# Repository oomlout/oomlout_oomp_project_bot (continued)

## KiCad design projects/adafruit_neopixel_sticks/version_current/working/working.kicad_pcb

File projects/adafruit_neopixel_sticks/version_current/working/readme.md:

# NeoPixel-Sticks by adafruit  
This is a harvested standardized copy of a project from github.  
The original project can be found at:  
https://github.com/adafruit/NeoPixel-Sticks  
Please consult that link for additional, details, files, and license information.  
Note: It was auto harvested and if the original repo had more than one board file or anything out of the ordinary the files here are likely not representative.

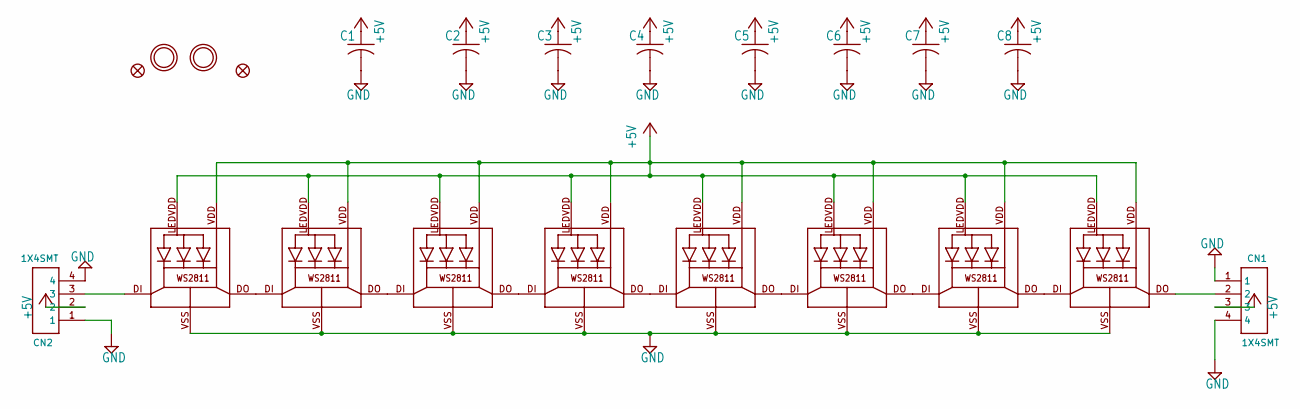
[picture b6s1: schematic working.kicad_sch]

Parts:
C1, C2, C3, C4, C5, C6, C7, C8: C-USC0805K; C0805K
CN1, CN2: 1X4SMT; 1X4-SMT
FID1, FID3: FIDUCIAL""; FIDUCIAL_1MM
LED1, LED2, LED3, LED4, LED5, LED6, LED7, LED8: WS28115050
U$2, U$3: MOUNTINGHOLE2.0; MOUNTINGHOLE_2.0_PLATED

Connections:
+5V: C1.1, C2.1, C3.1, C4.1, C5.1, C6.1, C7.1, C8.1, CN1.3, CN2.2, LED1.LEDVDD, LED1.VDD, LED2.LEDVDD, LED2.VDD, LED3.LEDVDD, LED3.VDD, LED4.LEDVDD, LED4.VDD, LED5.LEDVDD, LED5.VDD, LED6.LEDVDD, LED6.VDD, LED7.LEDVDD, LED7.VDD, LED8.LEDVDD, LED8.VDD
GND: C1.2, C2.2, C3.2, C4.2, C5.2, C6.2, C7.2, C8.2, CN1.1, CN1.4, CN2.1, CN2.4, LED1.VSS (GND), LED2.VSS (GND), LED3.VSS (GND), LED4.VSS (GND), LED5.VSS (GND), LED6.VSS (GND), LED7.VSS (GND), LED8.VSS (GND)
unnamed: LED1.DO, LED2.DI
unnamed: LED2.DO, LED3.DI
unnamed: LED3.DO, LED4.DI
unnamed: LED4.DO, LED5.DI
unnamed: LED5.DO, LED6.DI
unnamed: LED6.DO, LED7.DI
unnamed: LED7.DO, LED8.DI
unnamed: CN2.3, LED1.DI
unnamed: CN1.2, LED8.DO

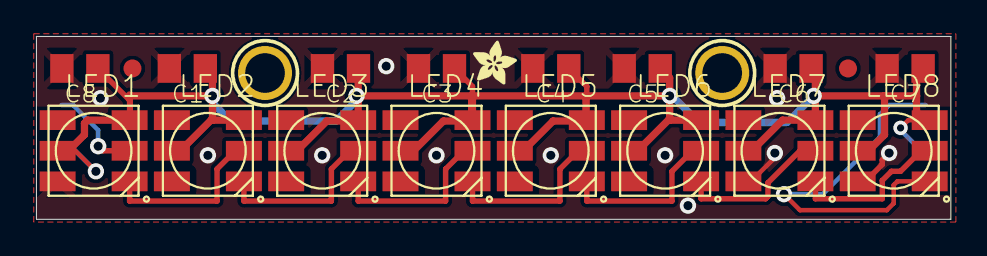
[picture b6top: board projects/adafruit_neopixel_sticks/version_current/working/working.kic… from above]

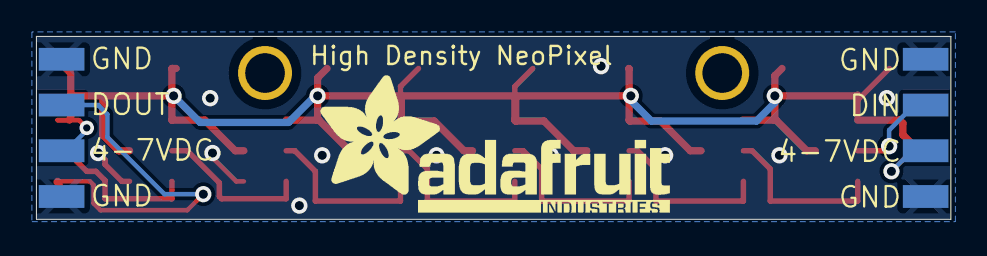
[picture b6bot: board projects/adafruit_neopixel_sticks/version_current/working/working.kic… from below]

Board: 2 copper layers, 50.8 x 10.2 mm, 24 parts (3 on the bottom side), 11 nets.

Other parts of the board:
U$1: ADAFRUIT_TEXT_20MM
U$4: ADAFRUIT_2.5MM

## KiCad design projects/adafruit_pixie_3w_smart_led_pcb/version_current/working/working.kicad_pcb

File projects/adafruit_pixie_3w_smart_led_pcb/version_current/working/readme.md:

# Pixie-3W-Smart-LED-PCB by adafruit  
This is a harvested standardized copy of a project from github.  
The original project can be found at:  
https://github.com/adafruit/Pixie-3W-Smart-LED-PCB  
Please consult that link for additional, details, files, and license information.  
Note: It was auto harvested and if the original repo had more than one board file or anything out of the ordinary the files here are likely not representative.

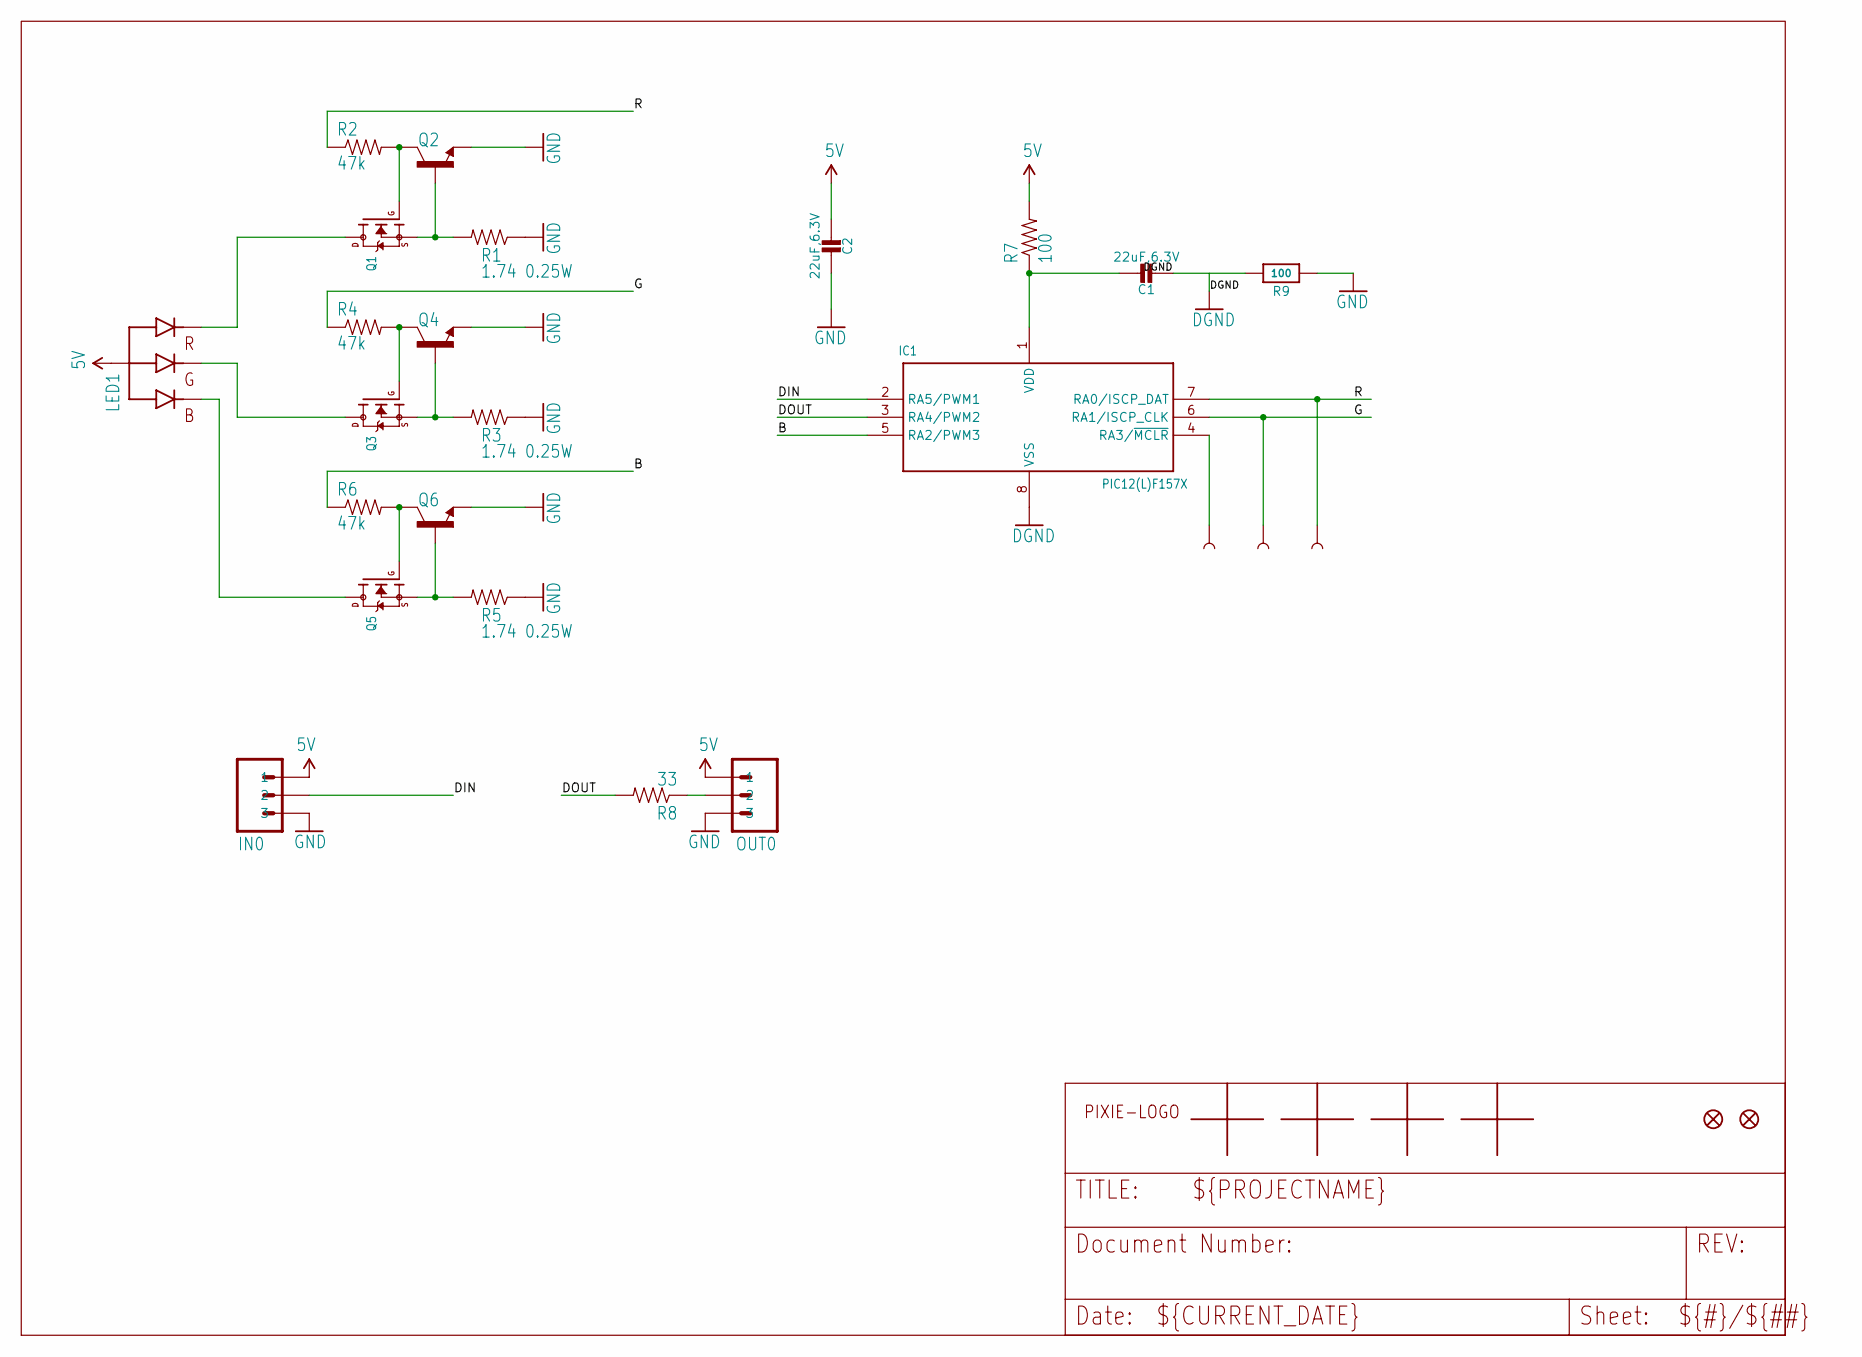
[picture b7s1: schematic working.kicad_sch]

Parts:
!MCLR0: TEST-POINT3X4; PAD.03X.04
C1, C2: 22uF,6.3V; _0805MP
IC1: PIC12(L)F157X; MSOP-8
IN0: M030.1PWR+SIG; 1X03-0.1PWR+SIG
LED1: RGBLED_CA; RGBLED3W4PIN
OUT0: M030.1PWR+SIG; 1X03-0.1PWR+SIG
PGC0: TEST-POINT3X4; PAD.03X.04
PGD0: TEST-POINT3X4; PAD.03X.04
Q1, Q3, Q5: IRLML2060TRPBF; SOT23-3
Q2, Q4, Q6: MMBT2222A; SOT23-3
R1, R3, R5: 1.74 0.25W; 1206
R2, R4, R6: 47k; 0603-RES
R7: 100; 0603-RES
R8: 33; 0603-RES
R9: 100; _0603MP
U$1, U$2, U$3, U$4: ALIGN_CROSS
U$5: PIXIE-LOGO
U$6, U$7: FIDUCIAL""; FIDUCIAL_1MM

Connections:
5V: C2.2, IN0.P$1 (1), LED1.ANODE (VCC), OUT0.P$1 (1), R7.2
B: IC1.5 (RA2/PWM3), R6.1
DGND: C1.2, IC1.8 (VSS), R9.2
DIN: IC1.2 (RA5/PWM1), IN0.P$2 (2)
DOUT: IC1.3 (RA4/PWM2), R8.2
G: IC1.6 (RA1/ISCP_CLK), PGC0.P$1, R4.1
GND: C2.1, IN0.P$3 (3), OUT0.P$3 (3), Q2.2 (E), Q4.2 (E), Q6.2 (E), R1.1, R3.1, R5.1, R9.1
unnamed: LED1.R (RED), Q1.3 (D)
unnamed: LED1.G (GREEN), Q3.3 (D)
unnamed: LED1.B (BLUE), Q5.3 (D)
unnamed: Q1.2 (S), Q2.1 (B), R1.2
unnamed: Q3.2 (S), Q4.1 (B), R3.2
unnamed: OUT0.P$2 (2), R8.1
unnamed: !MCLR0.P$1, IC1.4 (RA3/~MCLR)
unnamed: Q5.1 (G), Q6.3 (C), R6.2
unnamed: Q3.1 (G), Q4.3 (C), R4.2
unnamed: C1.1, IC1.1 (VDD), R7.1
unnamed: Q5.2 (S), Q6.1 (B), R5.2
unnamed: Q1.1 (G), Q2.3 (C), R2.2
R: IC1.7 (RA0/ISCP_DAT), PGD0.P$1, R2.1

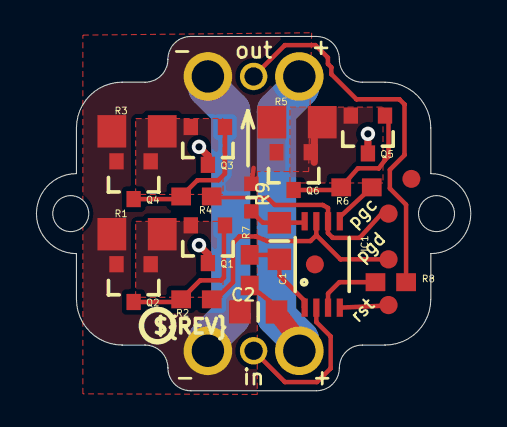
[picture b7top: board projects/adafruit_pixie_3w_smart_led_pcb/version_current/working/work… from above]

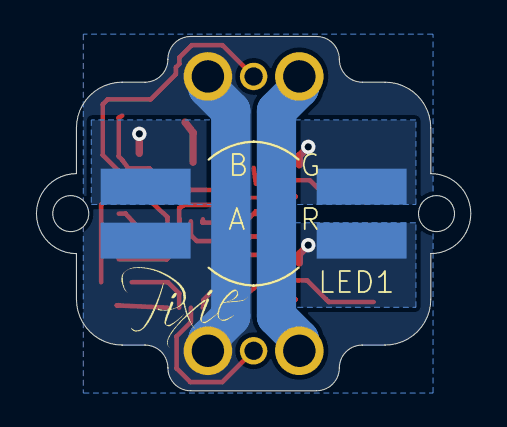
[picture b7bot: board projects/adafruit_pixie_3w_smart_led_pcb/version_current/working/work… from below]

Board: 16 copper layers, 24.1 x 19.7 mm, 34 parts (2 on the bottom side), 20 nets.

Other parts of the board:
@HOLE0, @HOLE1: (no value)
U$8: PCBFEAT-REV-040

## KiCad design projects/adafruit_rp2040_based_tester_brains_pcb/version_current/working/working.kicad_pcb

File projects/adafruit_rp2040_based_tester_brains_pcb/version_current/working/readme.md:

# OOMP Project  
## RP2040-Based-Tester-Brains-PCB  by adafruit  
  
oomp key: oomp_projects_flat_adafruit_rp2040_based_tester_brains_pcb  
(snippet of original readme)  
  
-- Adafruit RP2040 Based Tester Brains PCB  

PCB files for the Adafruit RP2040 Based Tester Brains.   
  
Format is EagleCAD schematic and board layout  
  
--- Description  
  
This board is what we use internally at Adafruit to program and test boards with microcontrollers on them.   
   * An [RP2040 Pico](https://www.adafruit.com/product/5525) (or perhaps PicoW?) is used to run the test software  
   * [Use a 16x2 LCD (ideally RGB backlight)](https://www.adafruit.com/product/398) for display output with color feedback such as green for pass, red for fail. RGB backlight is WS2811-controlled. Don't forget to set the contrast pot on first usage.  
   * Serial1 hardware UART has RX/TX pin switch to flip directions  
   * 1.9" TFT connector is placed but hasn't been tested or used yet  
   * Piezo buzzer can be used for audible feedback alerts  
   * STEMMA QT I2C port  
   * Big reset button  
   * Firmware files can be stored on MicroSD card which is slotted in.   
   * Connect the right hand side, either the 0.1" header or 18-pin EYESPI-like FPC connector to the device-under-test jig which can be different for each product.   
   * [USB Host testing is done with bitbang PIO support in TinyUSB](https://github.com/adafruit/Adafruit_TinyUSB_Arduino), USB 5V power can be turned on / off   
   * Use Philhower RP2040 core for programming  
   * The RP2040 brains can perform ESP32 programming, RP2040-via-USB, AVR ICSP/UPDI, or SWD DAP. [See the TestBed library for some   
  full source readme at [readme_src.md](readme_src.md)  
  
source repo at: [https://github.com/adafruit/RP2040-Based-Tester-Brains-PCB](https://github.com/adafruit/RP2040-Based-Tester-Brains-PCB)  
## Board  

## Schematic  

[schematic pdf](working_schematic.pdf)  
## Images

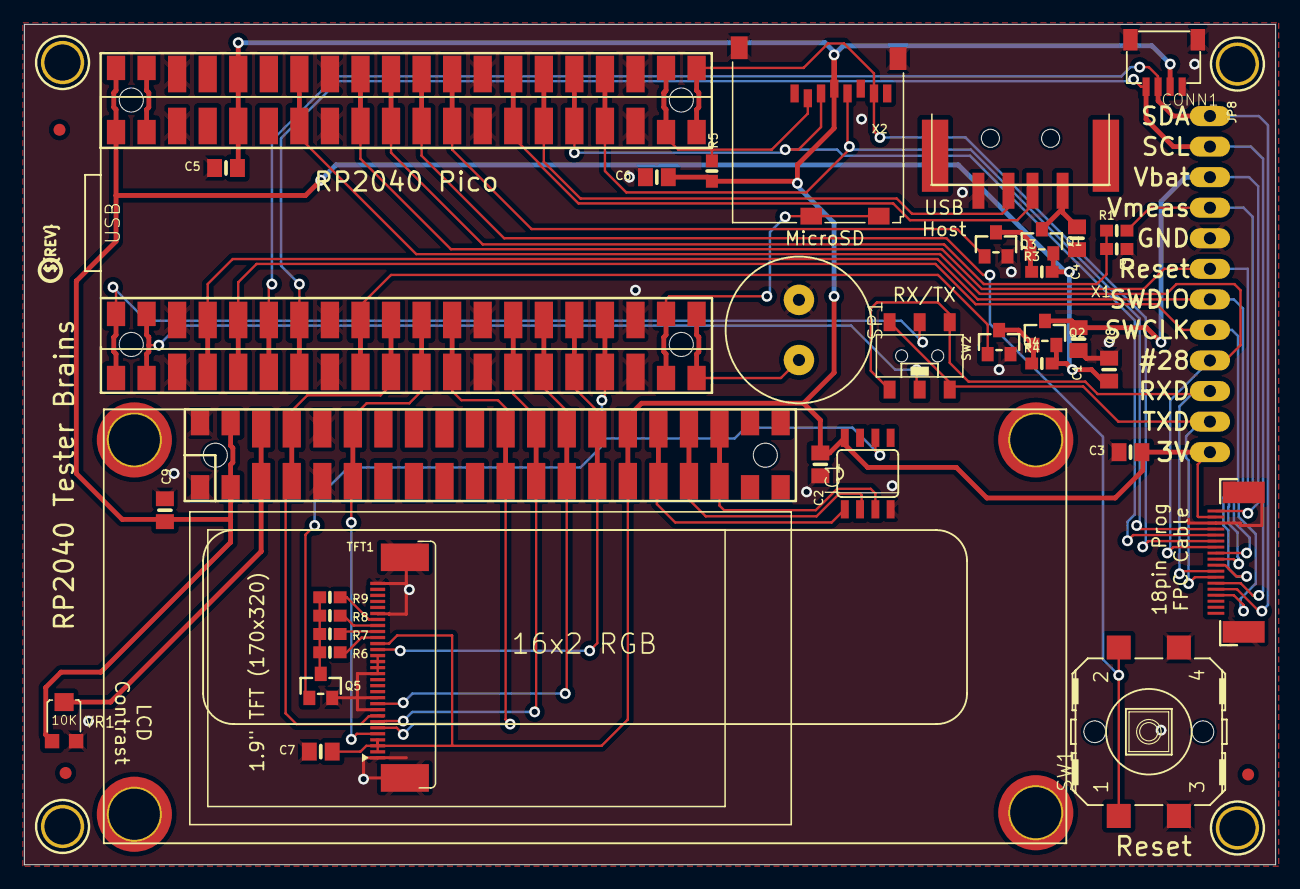
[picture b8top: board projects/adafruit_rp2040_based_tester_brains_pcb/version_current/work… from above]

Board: 2 copper layers, 104.0 x 69.8 mm, 48 parts (0 on the bottom side), 47 nets.

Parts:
C1, C2, C3, C4, C5, C6, C7, C8, C9: 10uF; 0805-NO
CB1: PICOWBELL_DUALSMT
CONN1: STEMMA_I2C_QT; JST_SH4
FID1, FID2, FID3: FIDUCIAL_1MM
IC1: WS2811-SOP8; SO08-SKINNYPADS
JP1: 16x2 LCD; 2X20_SMT_MALE
JP8: 1X12_OVAL
Q1, Q2: DMG34x5; SOT23-WIDE
Q3, Q4, Q5: BSS138; SOT23-WIDE
R1, R2, R3, R4, R5: 10K; 0603-NO
R6, R7, R8, R9: 27; 0603-NO
SP1: SPEAKER/PS12; PS12
SW1: 12mm SMT; B3F-40XX-SMT
SW2: DPDT SLIDE; EG1390
TFT1: DISP_LCD_ST7789_1.9IN_SS; TFT_1.9IN_170X320_30P_SS
TP1, TP2, TP3, TP4: SEWTAP_SMTNUTM3; SMT_NUT_3MM
U$7, U$8, U$9, U$10: MOUNTINGHOLE3.0THIN; MOUNTINGHOLE_3.0_PLATEDTHIN
U$13: PCBFEAT-REV-040
VR1: 10K Trimmer; TRIMPOT_BOURNS_TC33X-2
X1: USB A; USB_HOST-SMT
X2: MicroSD; MICROSD
X3: TESTER_PROGCABLE_FLIP; FPC_0.5MM_18PIN

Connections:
3.3V: C2.1, C3.1, C5.1, C6.1, C7.1, CB1.S71, CB1.S72, CONN1.2, IC1.8, JP1.29, JP1.30, JP8.12, R5.1, TFT1.2, TFT1.3, TFT1.4, TFT1.20, X2.4, X3.2
+5V: C8.1, C9.1, CB1.S79, CB1.S80, JP1.3, JP1.4, Q1.2, Q2.2, R3.2, R4.2, VR1.1
GND: C1.2, C2.2, C3.2, C4.2, C5.2, C6.2, C7.2, C8.2, C9.2, CB1.S5, CB1.S6, CB1.S15, CB1.S16, CB1.S25, CB1.S26, CB1.S35, CB1.S36, CB1.S45, CB1.S46, CB1.S55, CB1.S56, CB1.S65, CB1.S66, CB1.S75, CB1.S76, CONN1.1, CONN1.MT1, CONN1.MT2, IC1.4, JP1.1, JP1.2, JP1.9, JP1.10, JP8.5, Q3.2, Q4.2, Q5.2, R2.1, SP1.P$1, SW1.P$3, SW1.P$4, TFT1.1, TFT1.9, TFT1.11, TFT1.12, TFT1.13, TFT1.14, TFT1.15, TFT1.16, TFT1.17, TFT1.18, TFT1.25, TFT1.30, TFT1.MNT1, TFT1.MNT2, TP1.P$1, TP2.P$1, TP3.P$1, TP4.P$1, VR1.3, X1.GND, X2.6, X2.MT1, X2.MT2, X3.3, X3.SUPPORT1, X3.SUPPORT2
GPIO28: CB1.S67, CB1.S68, JP8.9, X3.7
LCD_BLUE: IC1.3, JP1.35, JP1.36
LCD_D4: CB1.S23, CB1.S24, JP1.21, JP1.22, TFT1.6
LCD_D5: CB1.S27, CB1.S28, JP1.23, JP1.24, TFT1.7
LCD_D6: CB1.S29, CB1.S30, JP1.25, JP1.26, TFT1.10
LCD_D7: CB1.S31, CB1.S32, JP1.27, JP1.28, TFT1.19
LCD_E: CB1.S21, CB1.S22, JP1.11, JP1.12, TFT1.5
LCD_GREEN: IC1.2, JP1.33, JP1.34
LCD_NEO: CB1.S33, CB1.S34, IC1.6, Q5.1
LCD_RED: IC1.1, JP1.31, JP1.32
LCD_RS: CB1.S19, CB1.S20, JP1.7, JP1.8, TFT1.8
LEDK: Q5.3, R6.1, R7.1, R8.1, R9.1
MISO: CB1.S41, CB1.S42, X2.7, X3.6
MOSI: CB1.S49, CB1.S50, X2.3, X3.5
unnamed: CB1.S39, CB1.S40, SP1.P$2
unnamed: R6.2, TFT1.21
unnamed: R7.2, TFT1.22
unnamed: R8.2, TFT1.23
unnamed: R9.2, TFT1.24
unnamed: JP1.5, JP1.6, VR1.2
RESET: CB1.S59, CB1.S60, SW1.P$1, SW1.P$2
RXD: CB1.S3, CB1.S4, SW2.P1
RXI: JP8.10, SW2.O2, SW2.S1, X3.11
SCK: CB1.S47, CB1.S48, X2.5, X3.4
SCL: CB1.S13, CB1.S14, CONN1.4, JP8.2, X3.13
SDA: CB1.S11, CB1.S12, CONN1.3, JP8.1, X3.14
SD_CD: CB1.S37, CB1.S38, X2.CD1, X2.CD2
SD_CS: CB1.S43, CB1.S44, R5.2, X2.2
SWCLK: CB1.S9, CB1.S10, JP8.8, X3.10
SWDIO: CB1.S7, CB1.S8, JP8.7, X3.9
TARGET_RESET: CB1.S63, CB1.S64, JP8.6, X3.8
TXD: CB1.S1, CB1.S2, SW2.P2
TXO: JP8.11, SW2.O1, SW2.S2, X3.12
USB_D+: CB1.S51, CB1.S52, X1.D+
USB_D-: CB1.S53, CB1.S54, X1.D-
VBAT: C1.1, JP8.3, Q2.3, X3.1
VBAT_SW: CB1.S17, CB1.S18, Q4.1
VMEAS: JP8.4, R1.2, X3.15
VMEAS_DIV2: CB1.S61, CB1.S62, R1.1, R2.2
VSYS: CB1.S77, CB1.S78
VUSB: C4.1, Q1.3, X1.VBUS
VUSB_SW: CB1.S57, CB1.S58, Q3.1
~VBAT_SW1: Q2.1, Q4.3, R4.1
~VBAT_SW2: Q1.1, Q3.3, R3.1
